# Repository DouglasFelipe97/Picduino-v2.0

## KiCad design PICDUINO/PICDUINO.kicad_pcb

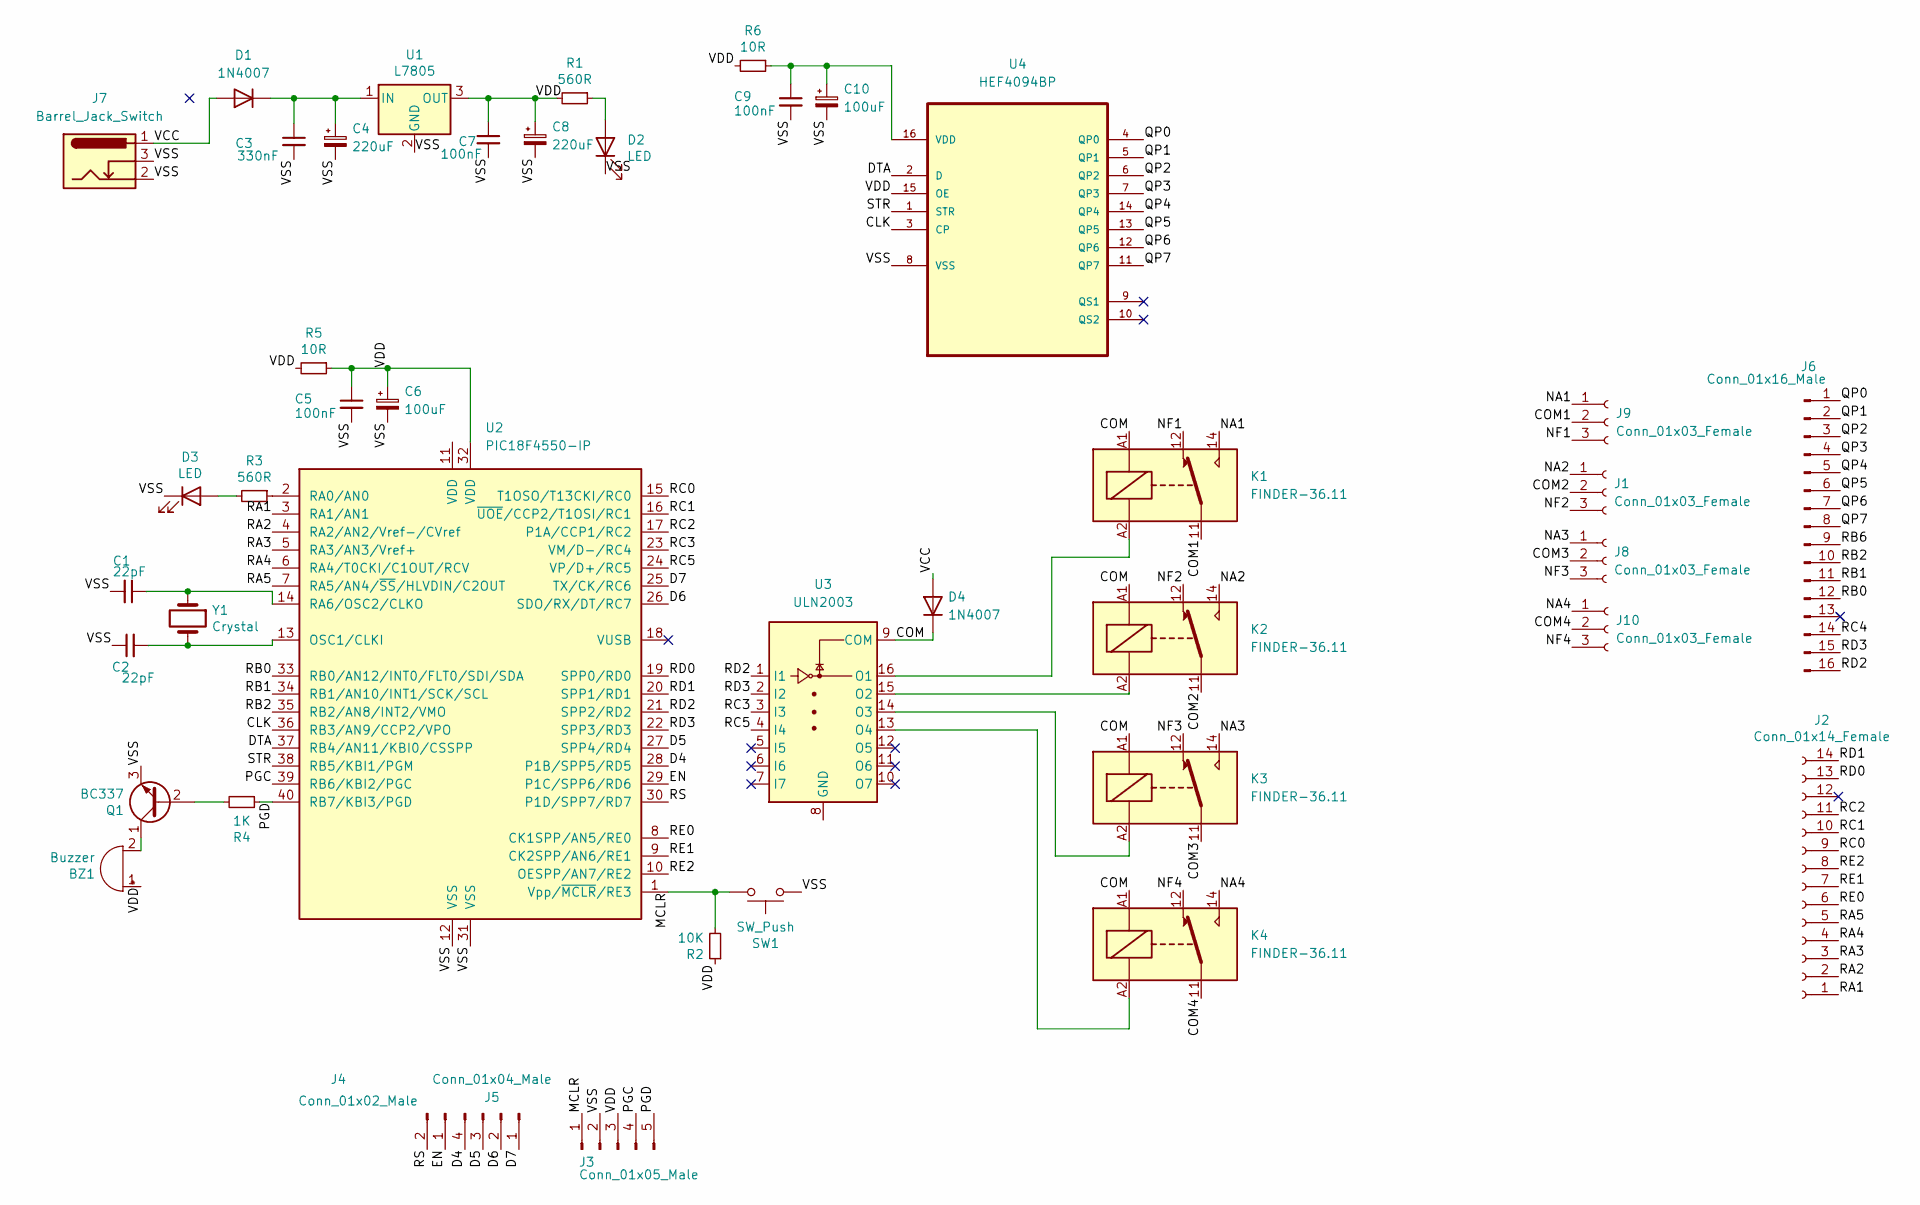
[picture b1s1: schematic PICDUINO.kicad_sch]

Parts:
BZ1: Buzzer; Buzzer_12x9.5RM7.6
C1, C2: 22pF; Cap_Disc_100nF
C3: 330nF; Cap_Disc_100nF
C4, C8: 220uF; Radial_Caneca_D6.3mm_220x16v
C5, C7, C9: 100nF; Cap_Disc_100nF
C6, C10: 100uF; Radial_Caneca_D5.0mm_100x16v
D1, D4: 1N4007; D_DO-41_SOD81_P10.16mm_Horizontal
D2, D3: LED; LED_D5.0mm
J1, J8, J9, J10: Conn_01x03_Female; borne3v
J2: Conn_01x14_Female; PinHeader_1x14_P2.54mm_Vertical
J3: Conn_01x05_Male; PinHeader_1x05_P2.54mm_Vertical
J4: Conn_01x02_Male; PinHeader_1x02_P2.54mm_Vertical
J5: Conn_01x04_Male; PinHeader_1x04_P2.54mm_Vertical
J6: Conn_01x16_Male; PinHeader_1x16_P2.54mm_Vertical
J7: Barrel_Jack_Switch; Conn_P4
K1, K2, K3, K4: FINDER-36.11; Relay_SPDT_Finder_36.11
Q1: BC337; TO-92_Inline
R1, R3: 560R; Res_1-2W_TermJust
R2: 10K; Res_1-2W_TermJust
R4: 1K; Res_1-2W_TermJust
R5, R6: 10R; Res_1-2W_TermJust
SW1: SW_Push; SW_DIP_SPSTx01_Slide_9.78x4.72mm_W7.62mm_P2.54mm
U1: L7805; TO-220-3_Vertical
U2: PIC18F4550-IP; DIP-40_W15.24mm
U3: ULN2003; DIP-16_W7.62mm
U4: HEF4094BP; DIP254P762X420-16; MPN HEF4094BP
Y1: Crystal; Crystal_HC18-U_Vertical

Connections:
/CLK: U2.36 (RB3/AN9/CCP2/VPO), U4.3 (CP)
/COM: D4.1 (K), K1.A1, K2.A1, K3.A1, K4.A1, U3.9 (COM)
/COM1: J9.2, K1.11
/COM2: J1.2, K2.11
/COM3: J8.2, K3.11
/COM4: J10.2, K4.11
/D4: J5.4, U2.28 (P1B/SPP5/RD5)
/D5: J5.3, U2.27 (SPP4/RD4)
/D6: J5.2, U2.26 (SDO/RX/DT/RC7)
/D7: J5.1, U2.25 (TX/CK/RC6)
/DTA: U2.37 (RB4/AN11/KBI0/CSSPP), U4.2 (D)
/EN: J4.1, U2.29 (P1C/SPP6/RD6)
/MCLR: J3.1, R2.2, SW1.2, U2.1 (Vpp/~MCLR/RE3)
/NA1: J9.1, K1.14
/NA2: J1.1, K2.14
/NA3: J8.1, K3.14
/NA4: J10.1, K4.14
/NF1: J9.3, K1.12
/NF2: J1.3, K2.12
/NF3: J8.3, K3.12
/NF4: J10.3, K4.12
/PGC: J3.4, U2.39 (RB6/KBI2/PGC)
/PGD: J3.5, R4.1, U2.40 (RB7/KBI3/PGD)
/QP0: J6.1, U4.4 (QP0)
/QP1: J6.2, U4.5 (QP1)
/QP2: J6.3, U4.6 (QP2)
/QP3: J6.4, U4.7 (QP3)
/QP4: J6.5, U4.14 (QP4)
/QP5: J6.6, U4.13 (QP5)
/QP6: J6.7, U4.12 (QP6)
/QP7: J6.8, U4.11 (QP7)
/RA1: J2.1, U2.3 (RA1/AN1)
/RA2: J2.2, U2.4 (RA2/AN2/Vref-/CVref)
/RA3: J2.3, U2.5 (RA3/AN3/Vref+)
/RA4: J2.4, U2.6 (RA4/T0CKI/C1OUT/RCV)
/RA5: J2.5, U2.7 (RA5/AN4/~SS/HLVDIN/C2OUT)
/RB0: J6.12, U2.33 (RB0/AN12/INT0/FLT0/SDI/SDA)
/RB1: J6.11, U2.34 (RB1/AN10/INT1/SCK/SCL)
/RB2: J6.10, U2.35 (RB2/AN8/INT2/VMO)
/RB6: J6.9
/RC0: J2.9, U2.15 (T1OSO/T13CKI/RC0)
/RC1: J2.10, U2.16 (~UOE/CCP2/T1OSI/RC1)
/RC2: J2.11, U2.17 (P1A/CCP1/RC2)
/RC3: U2.23 (VM/D-/RC4), U3.3 (I3)
/RC4: J6.14
/RC5: U2.24 (VP/D+/RC5), U3.4 (I4)
/RD0: J2.13, U2.19 (SPP0/RD0)
/RD1: J2.14, U2.20 (SPP1/RD1)
/RD2: J6.16, U2.21 (SPP2/RD2), U3.1 (I1)
/RD3: J6.15, U2.22 (SPP3/RD3), U3.2 (I2)
/RE0: J2.6, U2.8 (CK1SPP/AN5/RE0)
/RE1: J2.7, U2.9 (CK2SPP/AN6/RE1)
/RE2: J2.8, U2.10 (OESPP/AN7/RE2)
/RS: J4.2, U2.30 (P1D/SPP7/RD7)
/STR: U2.38 (RB5/KBI1/PGM), U4.1 (STR)
/VCC: D1.2 (A), D4.2 (A), J7.1
/VDD: BZ1.1 (-), C5.1, C6.1, C7.1, C8.1, J3.3, R1.2, R2.1, R5.1, R5.2, R6.2, U1.3 (OUT), U2.32 (VDD), U4.15 (OE)
/VSS: C1.2, C2.1, C3.2, C4.2, C5.2, C6.2, C7.2, C8.2, C9.2, C10.2, D2.1 (K), D3.1 (K), J3.2, J7.2, J7.3, Q1.3 (E), SW1.1, U1.2 (GND), U2.12 (VSS), U2.31 (VSS), U4.8 (VSS)
unnamed: BZ1.2 (+), Q1.1 (C)
unnamed: C1.1, U2.14 (RA6/OSC2/CLKO), Y1.1
unnamed: C2.2, U2.13 (OSC1/CLKI), Y1.2
unnamed: C3.1, C4.1, D1.1 (K), U1.1 (IN)
unnamed: C9.1, C10.1, R6.1, U4.16 (VDD)
unnamed: D2.2 (A), R1.1
unnamed: D3.2 (A), R3.2
unnamed: K1.A2, U3.16 (O1)
unnamed: K2.A2, U3.15 (O2)
unnamed: K3.A2, U3.14 (O3)
unnamed: K4.A2, U3.13 (O4)
unnamed: Q1.2 (B), R4.2
unnamed: R3.1, U2.2 (RA0/AN0)

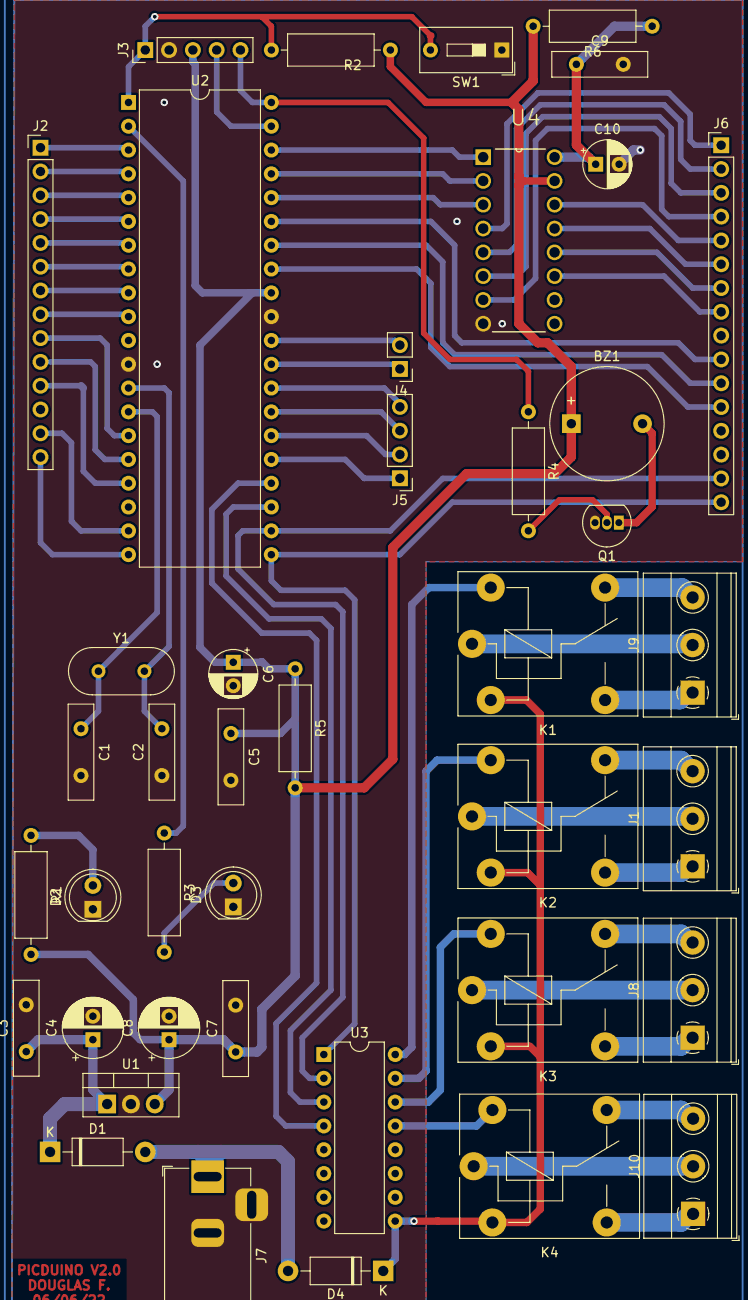
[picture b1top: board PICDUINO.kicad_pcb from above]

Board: 2 copper layers, 42 parts (0 on the bottom side), 69 nets.
